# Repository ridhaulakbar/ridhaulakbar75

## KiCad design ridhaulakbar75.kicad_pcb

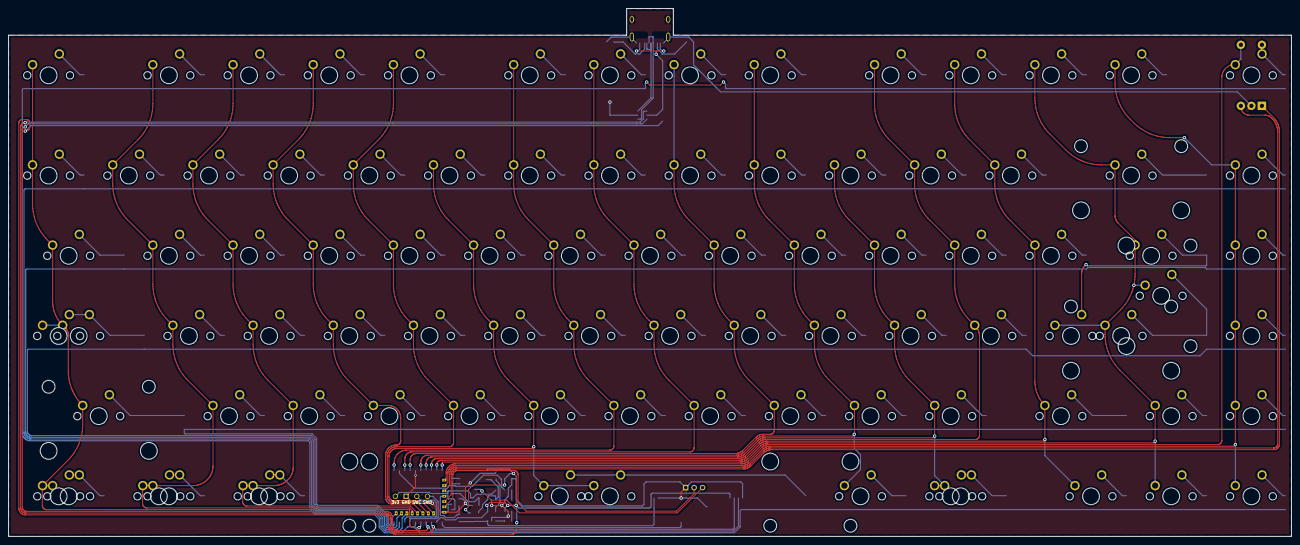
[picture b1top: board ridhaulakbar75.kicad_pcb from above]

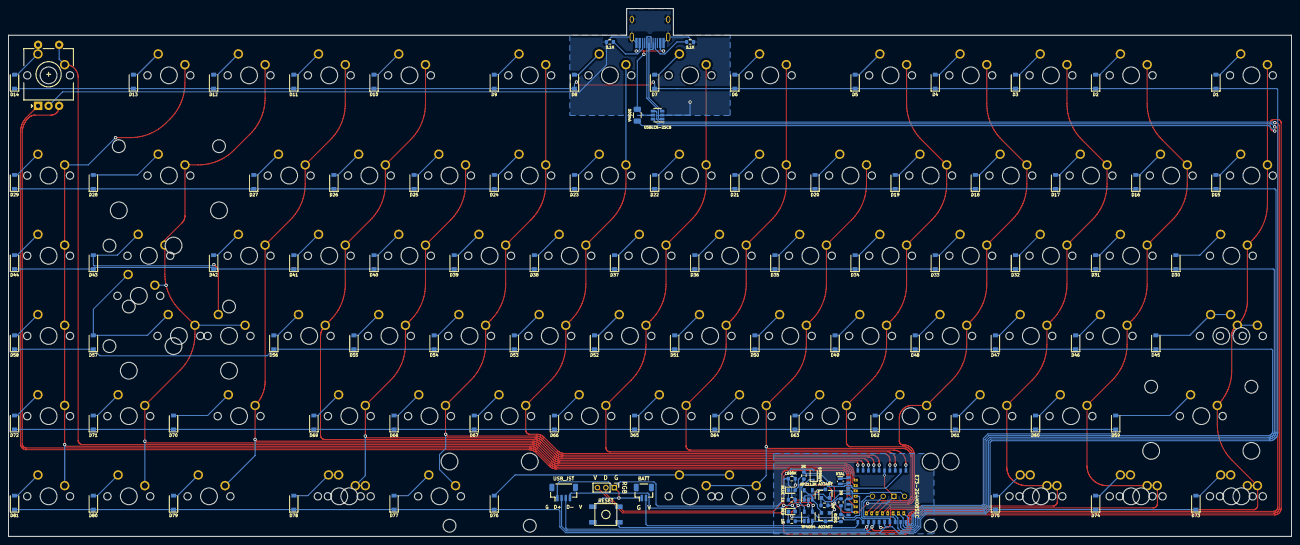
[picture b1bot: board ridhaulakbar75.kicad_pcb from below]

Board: 2 copper layers, 304.8 x 125.4 mm, 189 parts (107 on the bottom side), 131 nets.

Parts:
1K, 1K#2: 1K; R_0603_1608Metric
1N5819: 1N5819; D_SOD-323F
2K: 2K; R_0603_1608Metric
2M, 2M#2: 2M; R_0603_1608Metric
5.1K, 5.1K#2: 5.1K; R_0603_1608Metric
100K: 100k; R_0603_1608Metric
500mA: 500mA; Fuse_1206_3216Metric
820K: 820K; R_0603_1608Metric
AO3407, AO3407#2: AO3407; SOT-23
AP2112K: XC6220B331MR; SOT-23-5
BATT: Ex_Bat; JST_SH_BM02B-SRSS-TB_1x02-1MP_P1.00mm_Vertical
BLUE: BLUE; LED_0603_1608Metric
D1, D2, D3, D4, D5, D6, D7, D8, D9, D10, D11, D12, D13, D14, D15, D16, D17, D18, D19, D20, D21, D22, D23, D24, D25, D26, D27, D28, D29, D30, D31, D32, D33, D34, D35, D36, D37, D38, D39, D40, D41, D42, D43, D44, D45, D46, D47, D48, D49, D50, D51, D52, D53, D54, D55, D56, D57, D58, D59, D60, D61, D62, D63, D64, D65, D66, D67, D68, D69, D70, D71, D72, D73, D74, D75, D76, D77, D78, D79, D80, D81: 1N4148W; D_SOD-123-v2
J1: SWD; connector_swd
MX1: Esc; MXOnly-1U-NoLED
MX2: F1; MXOnly-1U-NoLED
MX3: F2; MXOnly-1U-NoLED
MX4: F3; MXOnly-1U-NoLED
MX5: F4; MXOnly-1U-NoLED
MX6: F5; MXOnly-1U-NoLED
MX7: F6; MXOnly-1U-NoLED
MX8: F7; MXOnly-1U-NoLED
MX9: F8; MXOnly-1U-NoLED
MX10: F9; MXOnly-1U-NoLED
MX11: F10; MXOnly-1U-NoLED
MX12: F11; MXOnly-1U-NoLED
MX13: F12; MXOnly-1U-NoLED
MX14: Delete; MXOnly-1U-NoLED
MX15: `; MXOnly-1U-NoLED
MX16: 1; MXOnly-1U-NoLED
MX17: 2; MXOnly-1U-NoLED
MX18: 3; MXOnly-1U-NoLED
MX19: 4; MXOnly-1U-NoLED
MX20: 5; MXOnly-1U-NoLED
MX21: 6; MXOnly-1U-NoLED
MX22: 7; MXOnly-1U-NoLED
MX23: 8; MXOnly-1U-NoLED
MX24: 9; MXOnly-1U-NoLED
MX25: 0; MXOnly-1U-NoLED
MX26: -; MXOnly-1U-NoLED
MX27: =; MXOnly-1U-NoLED
MX28: BackSpace; MXOnly-2U-NoLED
MX29: Home; MXOnly-1U-NoLED
MX30: Tab; MXOnly-1.5U-NoLED
MX31: Q; MXOnly-1U-NoLED
MX32: W; MXOnly-1U-NoLED
MX33: E; MXOnly-1U-NoLED
MX34: R; MXOnly-1U-NoLED
MX35: T; MXOnly-1U-NoLED
MX36: Y; MXOnly-1U-NoLED
MX37: U; MXOnly-1U-NoLED
MX38: I; MXOnly-1U-NoLED
MX39: O; MXOnly-1U-NoLED
MX40: P; MXOnly-1U-NoLED
MX41: [; MXOnly-1U-NoLED
MX42: ]; MXOnly-1U-NoLED
MX43: \; MXOnly-1.5U-NoLED
MX44: PgUp; MXOnly-1U-NoLED
MX45: CapsLock; MXOnly-1.75U-NoLED
MX46: A; MXOnly-1U-NoLED
MX47: S; MXOnly-1U-NoLED
MX48: D; MXOnly-1U-NoLED
MX49: F; MXOnly-1U-NoLED
MX50: G; MXOnly-1U-NoLED
MX51: H; MXOnly-1U-NoLED
MX52: J; MXOnly-1U-NoLED
MX53: K; MXOnly-1U-NoLED
MX54: L; MXOnly-1U-NoLED
MX55: ;; MXOnly-1U-NoLED
MX56: '; MXOnly-1U-NoLED
MX57: Enter; MXOnly-2.25U-NoLED
MX58: PgDn; MXOnly-1U-NoLED
MX59: LShift; MXOnly-2.25U-NoLED
MX60: Z; MXOnly-1U-NoLED
MX61: X; MXOnly-1U-NoLED
MX62: C; MXOnly-1U-NoLED
MX63: V; MXOnly-1U-NoLED
MX64: B; MXOnly-1U-NoLED
MX65: N; MXOnly-1U-NoLED
MX66: M; MXOnly-1U-NoLED
MX67: ,; MXOnly-1U-NoLED
MX68: .; MXOnly-1U-NoLED
MX69: /; MXOnly-1U-NoLED
MX70: RShift; MXOnly-1.75U-NoLED
MX71: Up; MXOnly-1U-NoLED
MX72: End; MXOnly-1U-NoLED
MX73: LCtrl; MXOnly-1.25U-NoLED
MX74: LGUI; MXOnly-1.25U-NoLED
MX75: LAlt; MXOnly-1.25U-NoLED
MX76: Space; MXOnly-6.25U-ReversedStabilizers-NoLED
MX77: RAlt; MXOnly-1.25U-NoLED
MX78: RCtrl; MXOnly-1.25U-NoLED
MX79: Left; MXOnly-1U-NoLED
MX80: Down; MXOnly-1U-NoLED
MX81: Right; MXOnly-1U-NoLED
RED: RED; LED_0603_1608Metric
RESET: RESET; SKQG-1155865
RGB: Underglow; PinHeader_1x03_P2.00mm_Vertical
SW1: Rotary_Encoder_Switch; RotaryEncoder_EC11-no-legs
TP4054: TP4054; SOT-23-5
U2: E73-2G4M08S1C-52840
USB1: HRO-TYPE-C-31-M-12; HRO-TYPE-C-31-M-12-HandSoldering
USBLC6-2SC6: USBLC6-2SC6; SOT-23-6
USB_JST: Ex_USB; JST_SH_BM04B-SRSS-TB_1x04-1MP_P1.00mm_Vertical
XTAL: 32.768kHz; Crystal_SMD_MicroCrystal_CM9V-T1A-2Pin_1.6x1.0mm

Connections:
BATTERY_PIN: 2M#2.1, 820K.2, U2.18
BLUE_LED: BLUE.2, U2.2
COL0: MX1.1, MX15.1, MX30.1, MX45.1, MX59.1, MX73.1, U2.33
COL1: MX2.1, MX16.1, MX31.1, MX46.1, MX60.1, MX74.1, U2.36
COL2: MX3.1, MX17.1, MX32.1, MX47.1, MX61.1, MX75.1, U2.34
COL3: MX4.1, MX18.1, MX33.1, MX48.1, MX62.1, U2.32
COL4: MX5.1, MX19.1, MX34.1, MX49.1, MX63.1, U2.30
COL5: MX20.1, MX35.1, MX50.1, MX64.1, MX76.1, U2.28
COL6: MX6.1, MX21.1, MX36.1, MX51.1, MX65.1, U2.1
COL7: MX7.1, MX22.1, MX37.1, MX52.1, MX66.1, U2.3
COL8: MX8.1, MX23.1, MX38.1, MX53.1, MX67.1, U2.4
COL9: MX9.1, MX24.1, MX39.1, MX54.1, MX68.1, MX77.1, U2.6
COL10: MX25.1, MX40.1, MX55.1, MX69.1, MX78.1, U2.7
COL11: MX10.1, MX26.1, MX41.1, MX56.1, U2.8
COL12: MX11.1, MX27.1, MX42.1, MX70.1, MX79.1, U2.9
COL13: MX12.1, MX28.1, MX43.1, MX57.1, MX71.1, MX80.1, U2.10
COL14: MX13.1, MX29.1, MX44.1, MX58.1, MX72.1, MX81.1, U2.14
COL15: MX14.1, SW1.S1, U2.12
DATA+: U2.31, USBLC6-2SC6.6, USB_JST.2
DATA-: U2.29, USBLC6-2SC6.4, USB_JST.3
EXT_VCC: AO3407#2.3, RGB.3
GND: 1K#2.1, 2K.1, 2M.2, 2M#2.2, 5.1K.1, 5.1K#2.1, 100K.2, AP2112K.2, BATT.1, J1.2, RESET.1, RGB.1, SW1.C, TP4054.2, U2.5, U2.21, U2.24, USB1.1, USB1.12, USB1.13, USBLC6-2SC6.2, USB_JST.1
unnamed: D1.2, MX1.2
unnamed: D2.2, MX2.2
unnamed: D3.2, MX3.2
unnamed: D4.2, MX4.2
unnamed: D5.2, MX5.2
unnamed: D6.2, MX6.2
unnamed: D7.2, MX7.2
unnamed: D8.2, MX8.2
unnamed: D9.2, MX9.2
unnamed: D10.2, MX10.2
unnamed: D11.2, MX11.2
unnamed: D12.2, MX12.2
unnamed: D13.2, MX13.2
unnamed: D14.2, MX14.2, SW1.S2
unnamed: D15.2, MX15.2
unnamed: D16.2, MX16.2
unnamed: D17.2, MX17.2
unnamed: D18.2, MX18.2
unnamed: D19.2, MX19.2
unnamed: D20.2, MX20.2
unnamed: D21.2, MX21.2
unnamed: D22.2, MX22.2
unnamed: D23.2, MX23.2
unnamed: D24.2, MX24.2
unnamed: D25.2, MX25.2
unnamed: D26.2, MX26.2
unnamed: D27.2, MX27.2
unnamed: D28.2, MX28.2
unnamed: D29.2, MX29.2
unnamed: D30.2, MX30.2
unnamed: D31.2, MX31.2
unnamed: D32.2, MX32.2
unnamed: D33.2, MX33.2
unnamed: D34.2, MX34.2
unnamed: D35.2, MX35.2
unnamed: D36.2, MX36.2
unnamed: D37.2, MX37.2
unnamed: D38.2, MX38.2
unnamed: D39.2, MX39.2
unnamed: D40.2, MX40.2
unnamed: D41.2, MX41.2
unnamed: D42.2, MX42.2
unnamed: D43.2, MX43.2
unnamed: D44.2, MX44.2
unnamed: D45.2, MX45.2
unnamed: D46.2, MX46.2
unnamed: D47.2, MX47.2
unnamed: D48.2, MX48.2
unnamed: D49.2, MX49.2
unnamed: D50.2, MX50.2
unnamed: D51.2, MX51.2
unnamed: D52.2, MX52.2
unnamed: D53.2, MX53.2
unnamed: D54.2, MX54.2
unnamed: D55.2, MX55.2
unnamed: D56.2, MX56.2
unnamed: D57.2, MX57.2
unnamed: D58.2, MX58.2
unnamed: D59.2, MX59.2
unnamed: D60.2, MX60.2
unnamed: D61.2, MX61.2
unnamed: D62.2, MX62.2
unnamed: D63.2, MX63.2
unnamed: D64.2, MX64.2
unnamed: D65.2, MX65.2
unnamed: D66.2, MX66.2
unnamed: D67.2, MX67.2
unnamed: D68.2, MX68.2
unnamed: D69.2, MX69.2
unnamed: D70.2, MX70.2
unnamed: D71.2, MX71.2
unnamed: D72.2, MX72.2
unnamed: D73.2, MX73.2
unnamed: D74.2, MX74.2
unnamed: D75.2, MX75.2
unnamed: D76.2, MX76.2
unnamed: D77.2, MX77.2
unnamed: D78.2, MX78.2
unnamed: D79.2, MX79.2
unnamed: D80.2, MX80.2
unnamed: D81.2, MX81.2
unnamed: 1K#2.2, BLUE.1
unnamed: 1N5819.1, AO3407.2, AP2112K.1, AP2112K.3
unnamed: 1K.2, RED.1
unnamed: 500mA.2, USB1.2, USB1.11, USBLC6-2SC6.5
unnamed: 5.1K#2.2, USB1.4
unnamed: 5.1K.2, USB1.10
unnamed: 1K.1, TP4054.1
unnamed: 2K.2, TP4054.5
unnamed: USB1.6, USB1.8, USBLC6-2SC6.1
unnamed: USB1.5, USB1.7, USBLC6-2SC6.3
unnamed: U2.11, XTAL.1
unnamed: U2.13, XTAL.2
POWER_PIN: 2M.1, AO3407#2.1, U2.17
RESET: RESET.2, U2.26
RGB: RGB.2, U2.22
ROW0: D1.1, D2.1, D3.1, D4.1, D5.1, D6.1, D7.1, D8.1, D9.1, D10.1, D11.1, D12.1, D13.1, D14.1, U2.38
ROW1: D15.1, D16.1, D17.1, D18.1, D19.1, D20.1, D21.1, D22.1, D23.1, D24.1, D25.1, D26.1, D27.1, D28.1, D29.1, U2.41
ROW2: D30.1, D31.1, D32.1, D33.1, D34.1, D35.1, D36.1, D37.1, D38.1, D39.1, D40.1, D41.1, D42.1, D43.1, D44.1, U2.40
ROW3: D45.1, D46.1, D47.1, D48.1, D49.1, D50.1, D51.1, D52.1, D53.1, D54.1, D55.1, D56.1, D57.1, D58.1, U2.43
ROW4: D59.1, D60.1, D61.1, D62.1, D63.1, D64.1, D65.1, D66.1, D67.1, D68.1, D69.1, D70.1, D71.1, D72.1, U2.42
ROW5: D73.1, D74.1, D75.1, D76.1, D77.1, D78.1, D79.1, D80.1, D81.1, U2.35
Rotary-A: SW1.A, U2.20
Rotary-B: SW1.B, U2.16
SWC: J1.3, U2.39
SWD: J1.4, U2.37
VBAT: 820K.1, AO3407.3, BATT.2, TP4054.3
VBUS: 1N5819.2, 100K.1, 500mA.1, AO3407.1, RED.2, TP4054.4, U2.27, USB_JST.4
nRF_VDD: AO3407#2.2, AP2112K.5, J1.1, U2.19, U2.23

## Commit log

2021-03-12 big update
2021-03-15 updae
2021-03-17 big update and revision
2021-03-18 final
2021-03-24 add usb c back and add iso
2021-03-25 bit of update
2021-03-25 add gerber.zip
